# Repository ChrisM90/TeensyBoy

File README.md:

New best FPS achieved 5.7 :-) 

First revision PCB design complete and awaiting fabrication.

Do To's:

1) Finish sound implementation.
2) Serious optimization and code cleanup.
3) Gameboy colour compatibility.
4) Cartridge connector to play real games?
5) Functionality to rip ROM's to SD card?
6) Proper hardware explanation and documentation.

If you feel inclined to donate:
Bitcoin:  1EkhsVgQydefFFrJgEuCpkJ9TY6QsAo3og

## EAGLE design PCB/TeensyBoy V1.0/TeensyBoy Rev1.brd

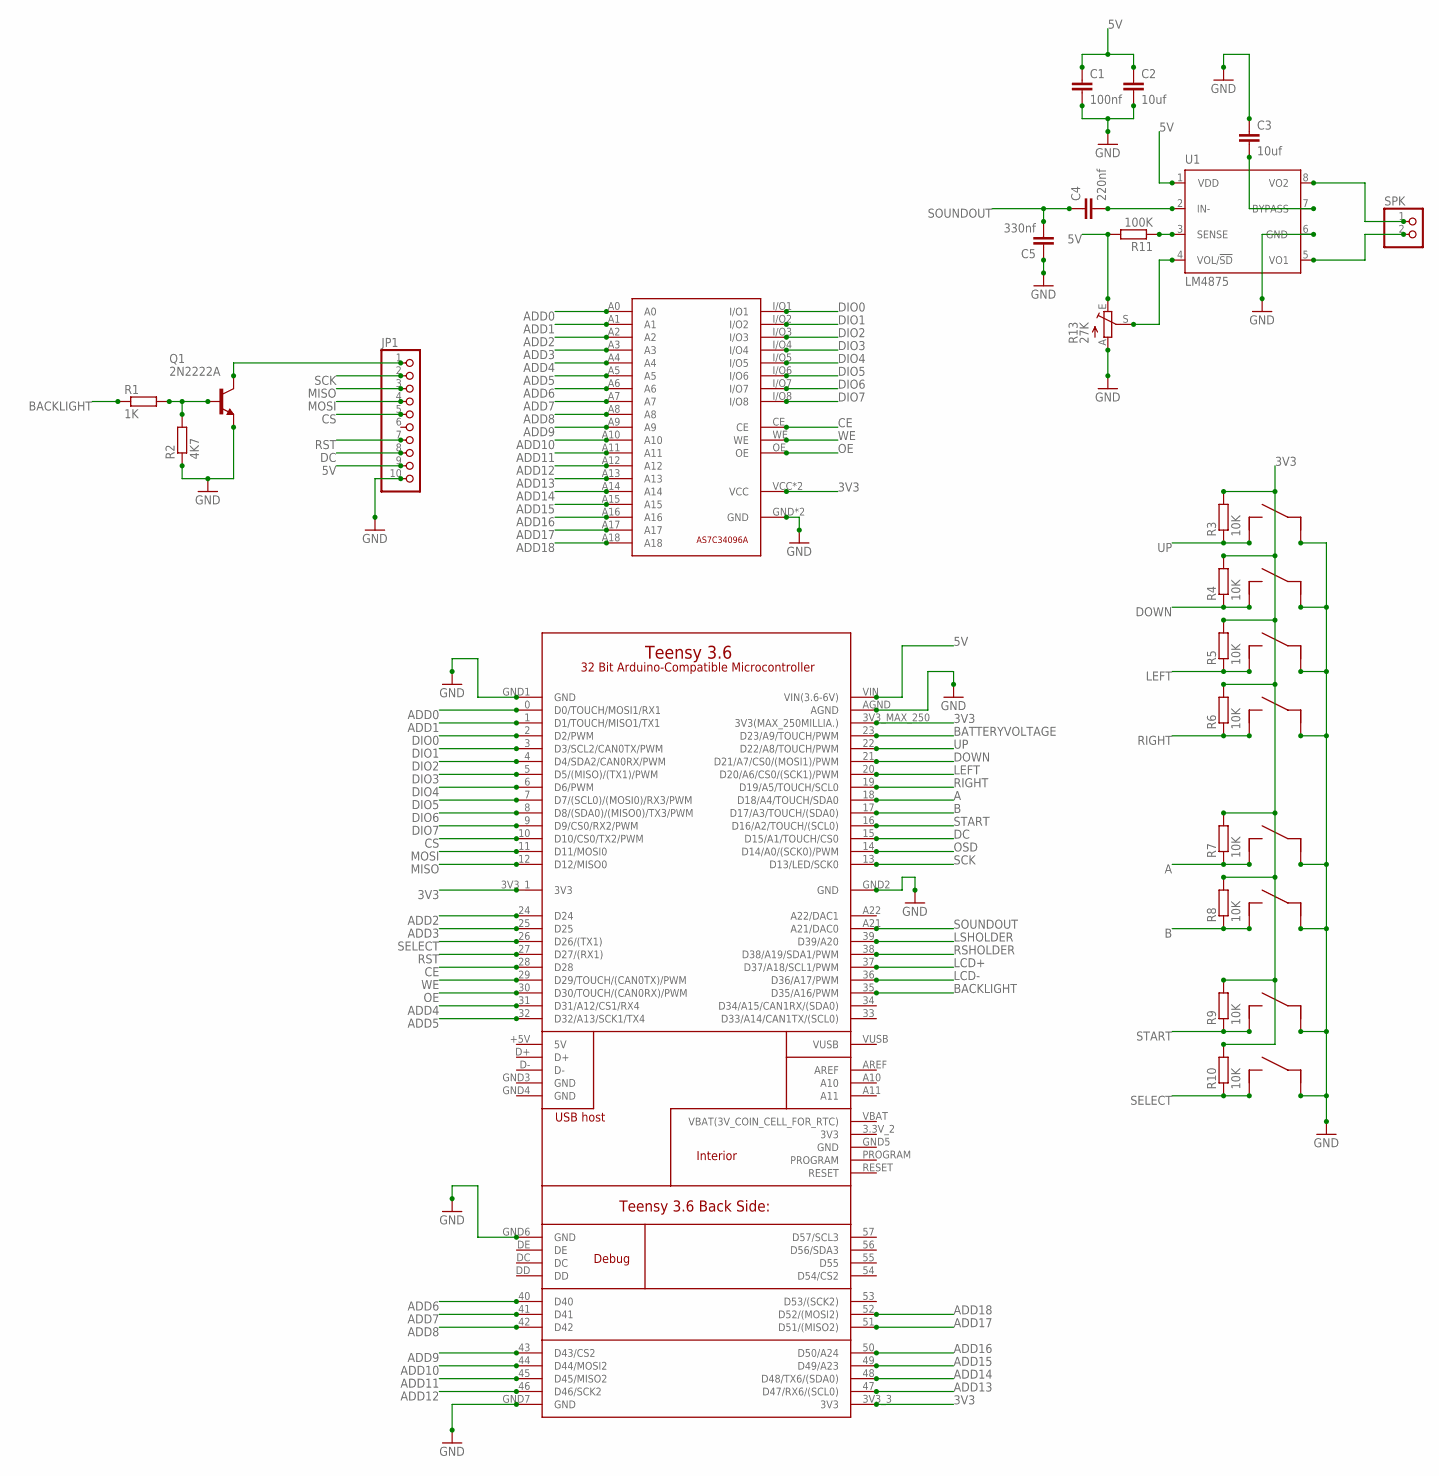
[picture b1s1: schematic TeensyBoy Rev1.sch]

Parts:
A: DTS-3
B: DTS-3
C1: 100nf; C0603K
C2, C3: 10uf; C0603K
C4: 220nf; C0603K
C5: 330nf; C0603K
DOWN: DTS-3
JP1: PINHD-1X10; 1X10
LEFT: DTS-3
Q1: 2N2222A; TO18
R1: 1K; R0603
R2: 4K7; R0603
R3, R4, R5, R6, R7, R8, R9, R10: 10K; R0603
R11: 100K; R0603
R13: 27K; CT6
RIGHT: DTS-3
SELECT: DTS-3
SPK: PINHD-1X2; 1X02
START: DTS-3
U1: LM4875; SO-8
U$1: AS7C34096A
U$2: TEENSY-3.6_FULL
UP: DTS-3

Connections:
3V3: R3.2, R4.2, R5.2, R6.2, R7.2, R8.2, R9.2, R10.2, U$1.VCC, U$1.VCC0 (VCC), U$2.3V3_1 (3V3), U$2.3V3_3 (3V3), U$2.3V3_MAX_250 (3V3(MAX_250MILLIA.))
5V: C1.1, C2.1, JP1.9, R11.2, R13.E, U1.1 (VDD), U$2.VIN (VIN(3.6-6V))
A: A.P$1, R7.1, U$2.18 (D18/A4/TOUCH/SDA0)
ADD0: U$1.A0, U$2.0 (D0/TOUCH/MOSI1/RX1)
ADD1: U$1.A1, U$2.1 (D1/TOUCH/MISO1/TX1)
ADD2: U$1.A2, U$2.24 (D24)
ADD3: U$1.A3, U$2.25 (D25)
ADD4: U$1.A4, U$2.31 (D31/A12/CS1/RX4)
ADD5: U$1.A5, U$2.32 (D32/A13/SCK1/TX4)
ADD6: U$1.A6, U$2.40 (D40)
ADD7: U$1.A7, U$2.41 (D41)
ADD8: U$1.A8, U$2.42 (D42)
ADD9: U$1.A9, U$2.43 (D43/CS2)
ADD10: U$1.A10, U$2.44 (D44/MOSI2)
ADD11: U$1.A11, U$2.45 (D45/MISO2)
ADD12: U$1.A12, U$2.46 (D46/SCK2)
ADD13: U$1.A13, U$2.47 (D47/RX6/(SCL0))
ADD14: U$1.A14, U$2.48 (D48/TX6/(SDA0))
ADD15: U$1.A15, U$2.49 (D49/A23)
ADD16: U$1.A16, U$2.50 (D50/A24)
ADD17: U$1.A17, U$2.51 (D51/(MISO2))
ADD18: U$1.A18, U$2.52 (D52/(MOSI2))
B: B.P$1, R8.1, U$2.17 (D17/A3/TOUCH/(SDA0))
BACKLIGHT: R1.1, U$2.35 (D35/A16/PWM)
BATTERYVOLTAGE: U$2.23 (D23/A9/TOUCH/PWM)
CE: U$1.CE, U$2.28 (D28)
CS: JP1.5, U$2.10 (D10/CS0/TX2/PWM)
DC: JP1.8, U$2.15 (D15/A1/TOUCH/CS0)
DIO0: U$1.I/O1, U$2.2 (D2/PWM)
DIO1: U$1.I/O2, U$2.3 (D3/SCL2/CAN0TX/PWM)
DIO2: U$1.I/O3, U$2.4 (D4/SDA2/CAN0RX/PWM)
DIO3: U$1.I/O4, U$2.5 (D5/(MISO)/(TX1)/PWM)
DIO4: U$1.I/O5, U$2.6 (D6/PWM)
DIO5: U$1.I/O6, U$2.7 (D7/(SCL0)/(MOSI0)/RX3/PWM)
DIO6: U$1.I/O7, U$2.8 (D8/(SDA0)/(MISO0)/TX3/PWM)
DIO7: U$1.I/O8, U$2.9 (D9/CS0/RX2/PWM)
DOWN: DOWN.P$1, R4.1, U$2.21 (D21/A7/CS0/(MOSI1)/PWM)
GND: A.P$2, B.P$2, C1.2, C2.2, C3.1, C5.1, DOWN.P$2, JP1.10, LEFT.P$2, Q1.1 (E), R2.1, R13.A, RIGHT.P$2, SELECT.P$2, START.P$2, U1.6 (GND), U$1.GND, U$1.GND0 (GND), U$2.AGND, U$2.GND1 (GND), U$2.GND2 (GND), U$2.GND6 (GND), U$2.GND7 (GND), UP.P$2
LCD+: U$2.37 (D37/A18/SCL1/PWM)
LCD-: U$2.36 (D36/A17/PWM)
LEFT: LEFT.P$1, R5.1, U$2.20 (D20/A6/CS0/(SCK1)/PWM)
LSHOLDER: U$2.39 (D39/A20)
MISO: JP1.3, U$2.12 (D12/MISO0)
MOSI: JP1.4, U$2.11 (D11/MOSI0)
unnamed: JP1.1, Q1.3 (C)
unnamed: Q1.2 (B), R1.2, R2.2
unnamed: C3.2, U1.7 (BYPASS)
unnamed: C4.2, U1.2 (IN-)
unnamed: R11.1, U1.3 (SENSE)
unnamed: SPK.1, U1.8 (VO2)
unnamed: SPK.2, U1.5 (VO1)
unnamed: R13.S, U1.4 (VOL/!SD)
OE: U$1.OE, U$2.30 (D30/TOUCH/(CAN0RX)/PWM)
OSD: U$2.14 (D14/A0/(SCK0)/PWM)
RIGHT: R6.1, RIGHT.P$1, U$2.19 (D19/A5/TOUCH/SCL0)
RSHOLDER: U$2.38 (D38/A19/SDA1/PWM)
RST: JP1.7, U$2.27 (D27/(RX1))
SCK: JP1.2, U$2.13 (D13/LED/SCK0)
SELECT: R10.1, SELECT.P$1, U$2.26 (D26/(TX1))
SOUNDOUT: C4.1, C5.2, U$2.A21 (A21/DAC0)
START: R9.1, START.P$1, U$2.16 (D16/A2/TOUCH/(SCL0))
UP: R3.1, U$2.22 (D22/A8/TOUCH/PWM), UP.P$1
WE: U$1.WE, U$2.29 (D29/TOUCH/(CAN0TX)/PWM)

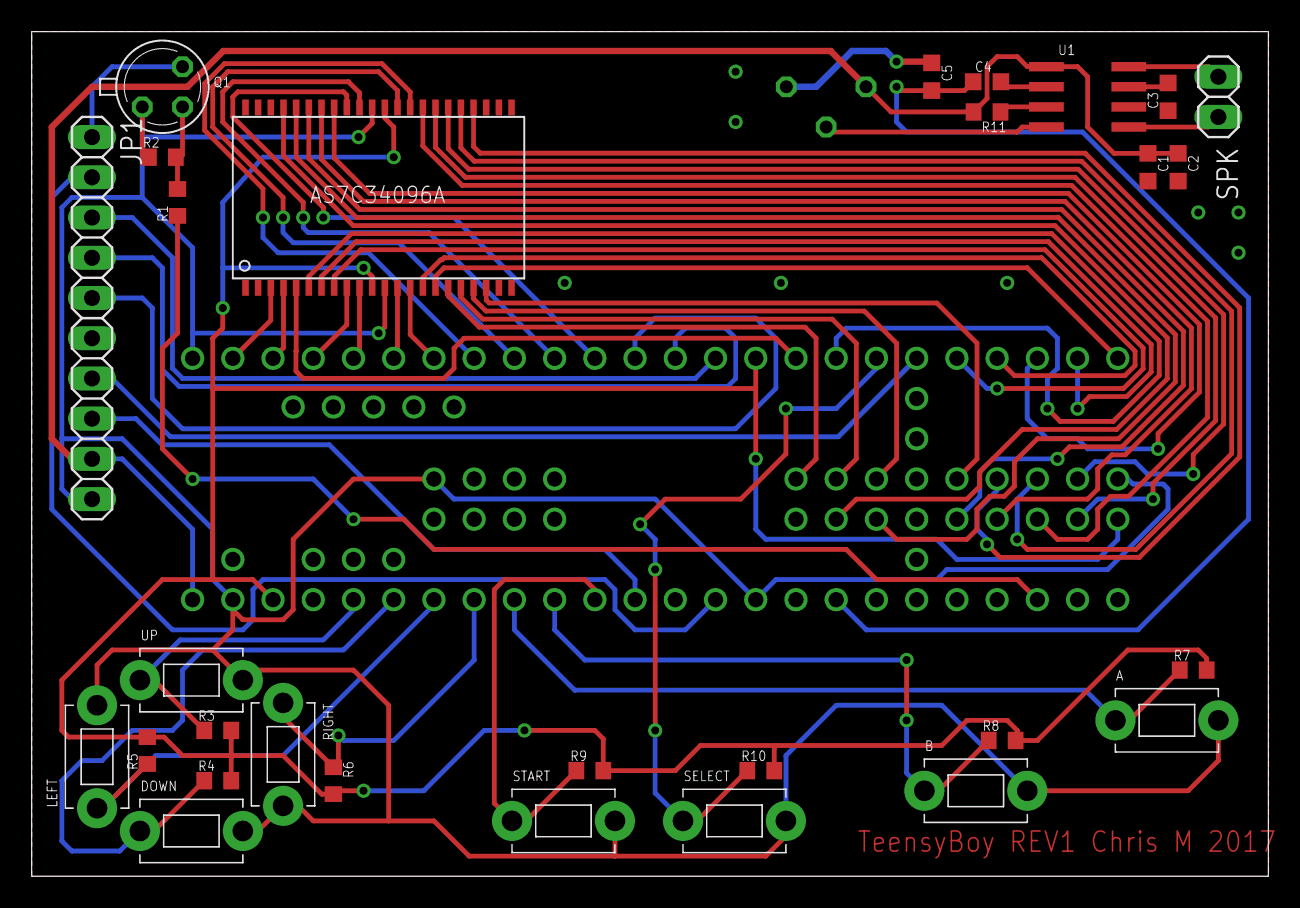
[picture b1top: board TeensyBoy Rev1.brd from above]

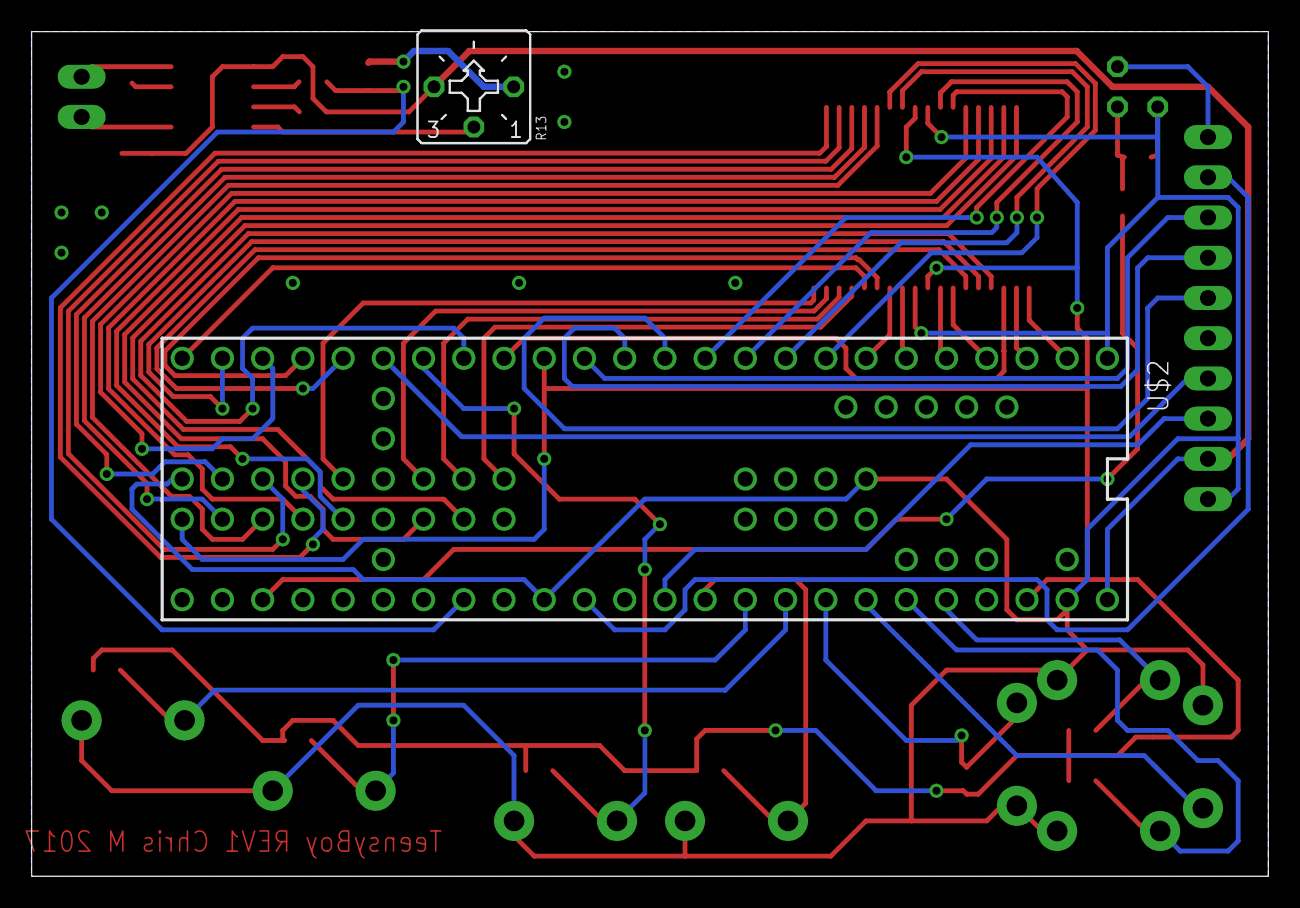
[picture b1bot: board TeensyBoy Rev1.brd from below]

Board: 2 copper layers, 78.1 x 53.3 mm, 31 parts (2 on the bottom side), 57 nets.

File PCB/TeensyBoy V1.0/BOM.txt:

Part     Value          Package

A        DTS-3          DTS-3
B        DTS-3          DTS-3
C1       100nf          C0603K
C2       10uf           C0603K
C3       10uf           C0603K
C4       220nf          C0603K
C5       330nf          C0603K
DOWN     DTS-3          DTS-3
JP1                     1X10
LEFT     DTS-3          DTS-3
Q1       2N2222A        TO18
R1       1K             R0603
R2       4K7            R0603
R3       10K            R0603
R4       10K            R0603
R5       10K            R0603
R6       10K            R0603
R7       10K            R0603
R8       10K            R0603
R9       10K            R0603
R10      10K            R0603
R11      100K           R0603
R13      27K            CT6
RIGHT    DTS-3          DTS-3
SELECT   DTS-3          DTS-3
SPK                     1X02
START    DTS-3          DTS-3 
U$1      AS7C34096A     AS7C34096A
U$2                     TEENSY-3.6_FULL
U1       LM4875         SO-8
UP       DTS-3          DTS-3

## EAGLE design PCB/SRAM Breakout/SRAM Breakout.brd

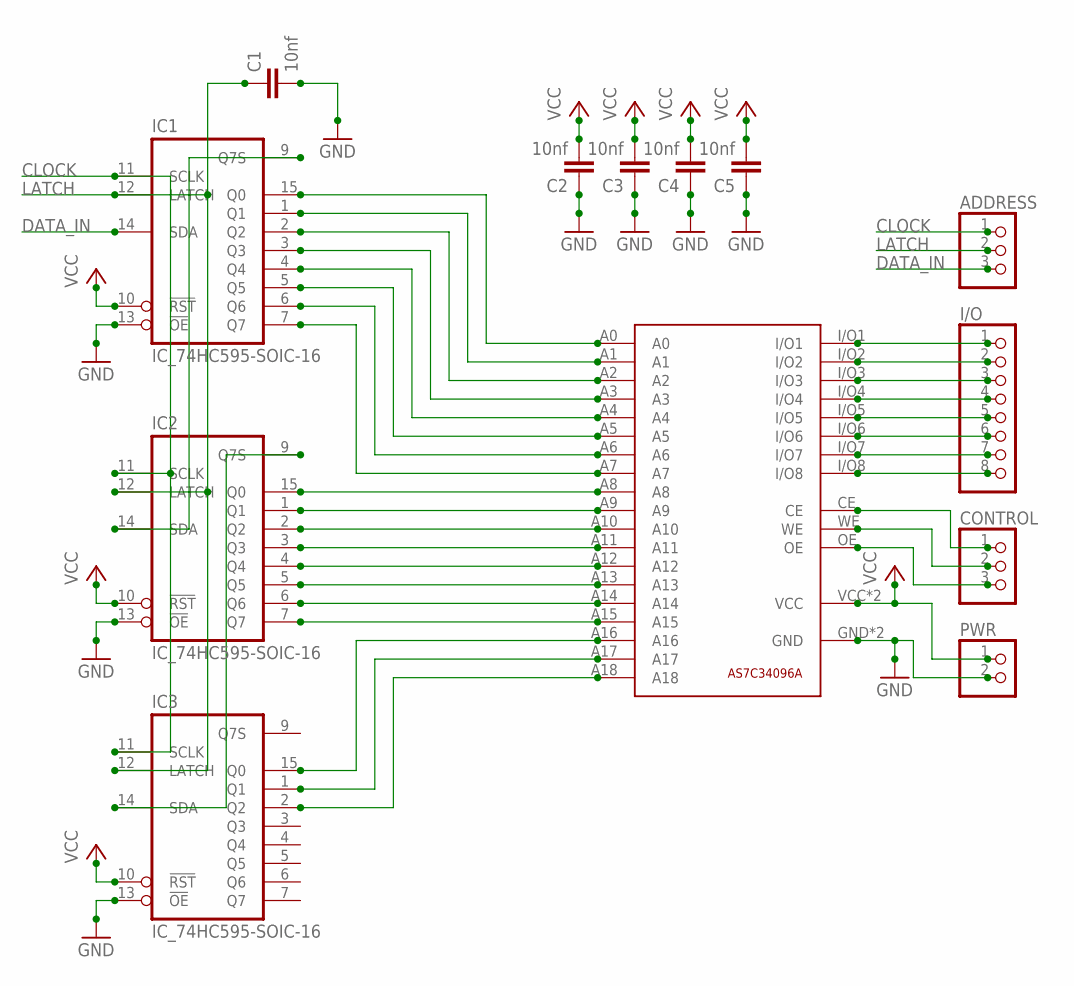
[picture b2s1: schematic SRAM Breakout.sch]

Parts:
ADDRESS: PINHD-1X3/90; 1X03/90
C1, C2, C3, C4, C5: 10nf; C0603
CONTROL: PINHD-1X3/90; 1X03/90
I/O: PINHD-1X8/90; 1X08/90
IC1, IC2, IC3: IC_74HC595-SOIC-16; SOIC-16
PWR: PINHD-1X2/90; 1X02/90
U$1: AS7C34096A

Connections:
CLOCK: ADDRESS.1, IC1.11 (SCLK), IC2.11 (SCLK), IC3.11 (SCLK)
DATA_IN: ADDRESS.3, IC1.14 (SDA)
GND: C1.2, C2.1, C3.1, C4.1, C5.1, IC1.13 (!OE), IC2.13 (!OE), IC3.13 (!OE), PWR.2, U$1.GND, U$1.GND0 (GND)
LATCH: ADDRESS.2, C1.1, IC1.12 (LATCH), IC2.12 (LATCH), IC3.12 (LATCH)
unnamed: IC1.9 (Q7S), IC2.14 (SDA)
unnamed: IC2.9 (Q7S), IC3.14 (SDA)
unnamed: I/O.1, U$1.I/O1
unnamed: IC1.15 (Q0), U$1.A0
unnamed: IC1.1 (Q1), U$1.A1
unnamed: IC1.2 (Q2), U$1.A2
unnamed: IC1.3 (Q3), U$1.A3
unnamed: IC1.4 (Q4), U$1.A4
unnamed: IC1.5 (Q5), U$1.A5
unnamed: IC1.6 (Q6), U$1.A6
unnamed: IC1.7 (Q7), U$1.A7
unnamed: IC2.15 (Q0), U$1.A8
unnamed: IC2.1 (Q1), U$1.A9
unnamed: IC2.2 (Q2), U$1.A10
unnamed: IC2.3 (Q3), U$1.A11
unnamed: IC2.4 (Q4), U$1.A12
unnamed: IC2.5 (Q5), U$1.A13
unnamed: IC2.6 (Q6), U$1.A14
unnamed: IC2.7 (Q7), U$1.A15
unnamed: IC3.15 (Q0), U$1.A16
unnamed: IC3.1 (Q1), U$1.A17
unnamed: IC3.2 (Q2), U$1.A18
unnamed: I/O.2, U$1.I/O2
unnamed: I/O.3, U$1.I/O3
unnamed: I/O.4, U$1.I/O4
unnamed: I/O.5, U$1.I/O5
unnamed: I/O.6, U$1.I/O6
unnamed: I/O.7, U$1.I/O7
unnamed: I/O.8, U$1.I/O8
unnamed: CONTROL.1, U$1.CE
unnamed: CONTROL.2, U$1.WE
unnamed: CONTROL.3, U$1.OE
VCC: C2.2, C3.2, C4.2, C5.2, IC1.10 (!RST), IC2.10 (!RST), IC3.10 (!RST), PWR.1, U$1.VCC, U$1.VCC0 (VCC)

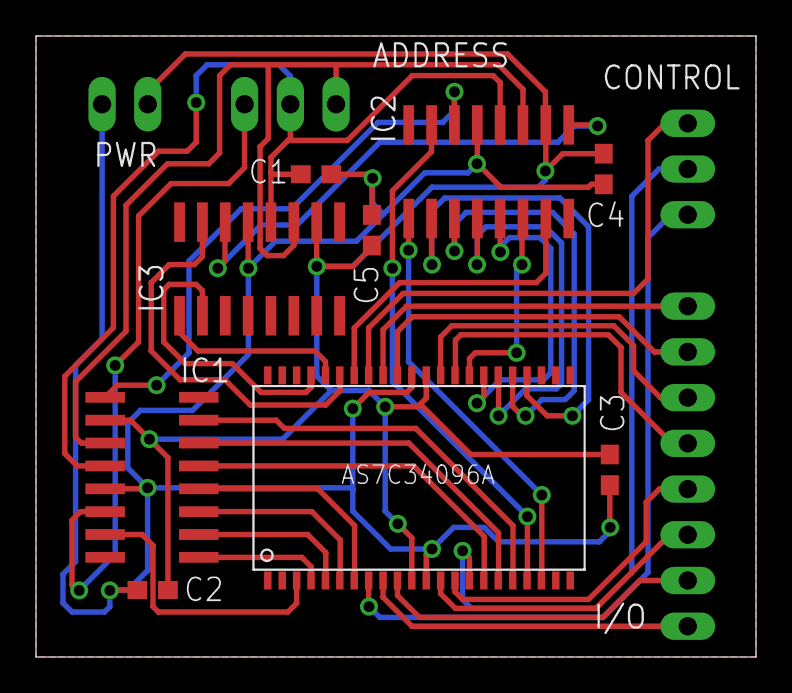
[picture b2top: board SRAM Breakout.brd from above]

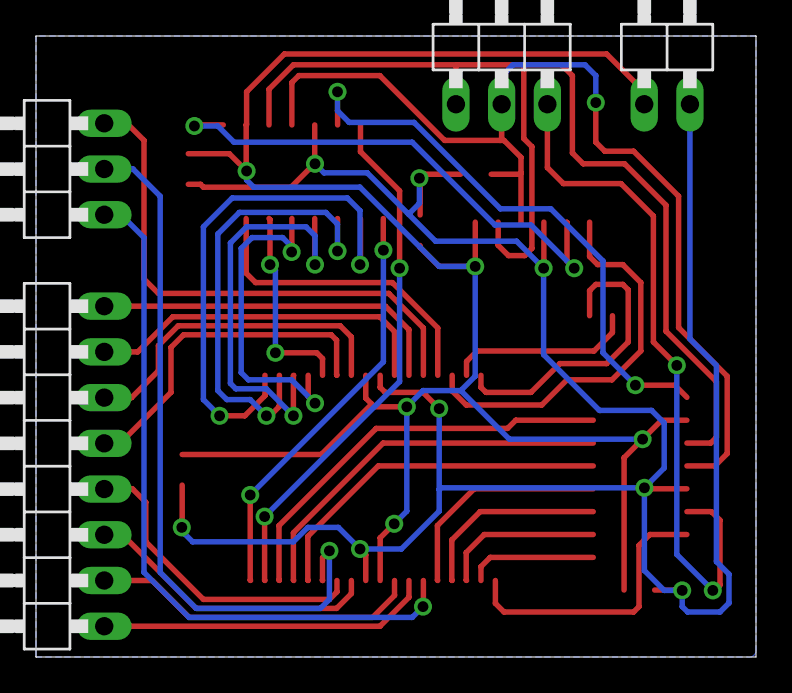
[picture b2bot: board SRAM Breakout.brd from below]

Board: 2 copper layers, 40.0 x 34.5 mm, 13 parts (4 on the bottom side), 37 nets.

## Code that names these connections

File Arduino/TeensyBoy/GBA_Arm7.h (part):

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  //Memory Address Time Seq: 0.40us
  
  //           BITMASK       PORTSET       PORTCLR
  // ADD0 0   //(1 << 16)    GPIOB_PSOR    GPIOB_PCOR
  // ADD1 1   //(1 << 17)    GPIOB_PSOR    GPIOB_PCOR
  // ADD2 24  //(1 << 26)    GPIOE_PSOR    GPIOE_PCOR
  // ADD3 25  //(1 << 5)     GPIOA_PSOR    GPIOA_PCOR
  // ADD4 31  //(1 << 10)    GPIOB_PSOR    GPIOB_PCOR
  // ADD5 32  //(1 << 11)    GPIOB_PSOR    GPIOB_PCOR
  // ADD6 40  //(1 << 28)    GPIOA_PSOR    GPIOA_PCOR
  // ADD7 41  //(1 << 29)    GPIOA_PSOR    GPIOA_PCOR 
  // ADD8 42  //(1 << 26)    GPIOA_PSOR    GPIOA_PCOR 
  // ADD9 43  //(1 << 20)    GPIOB_PSOR    GPIOB_PCOR
  // ADD10 44 //(1 << 22)    GPIOB_PSOR    GPIOB_PCOR
  // ADD11 45 //(1 << 23)    GPIOB_PSOR    GPIOB_PCOR
  // ADD12 46 //(1 << 21)    GPIOB_PSOR    GPIOB_PCOR
  // ADD13 47 //(1 << 8)     GPIOD_PSOR    GPIOD_PCOR 
  // ADD14 48 //(1 << 9)     GPIOD_PSOR    GPIOD_PCOR 
  // ADD15 49 //(1 << 4)     GPIOB_PSOR    GPIOB_PCOR
  // ADD16 50 //(1 << 5)     GPIOB_PSOR    GPIOB_PCOR 
  // ADD17 51 //(1 << 14)    GPIOD_PSOR    GPIOD_PCOR
  // ADD18 52 //(1 << 13)    GPIOD_PSOR    GPIOD_PCOR

  //GPIOB
  //Bit   24 23 22 21 20 19 18 17 16 15 14 13 12 11 10 9  8  7  6  5  4  3  2  1  0
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  }

  GPIOA_PCOR |= 12288; //Clear PORTA Data Lines
  GPIOA_PSOR |= (((value >> 1) & 0x03) << 12); //DIO1 & DIO2

  if(((value >> 3) & 0x01)) //DIO3
  {
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  }

  GPIOD_PCOR |= 12; //Clear PORTD Data Lines
  GPIOD_PSOR |= (((value >> 5) & 0x03) << 2); //DIO5 & DIO6

  if(((value >> 7) & 0x01)) //DIO7
  {
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  }

  //Read IO Pins
  value = (GPIOD_PDIR & (1 << 0) ? 1 : 0);            //DIO0
  value |= (((GPIOA_PDIR >> 12) & 0x03) << 1);        //DIO1 & DIO2
  value |= ((GPIOD_PDIR & (1 << 7) ? 1 : 0) << 3);    //DIO3
  value |= ((GPIOD_PDIR & (1 << 4) ? 1 : 0) << 4);    //DIO4
  value |= (((GPIOD_PDIR >> 2) & 0x03) << 5);         //DIO5 & DIO6
  value |= ((GPIOC_PDIR & (1 << 3) ? 1 : 0) << 7);    //DIO7
  
  return value;
}
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
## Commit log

2017-03-15 :space_invader: Added .gitattributes & .gitignore files
2017-03-15 SRAM Breakout Eagle Files Added
2017-03-16 Added Pinout Information
2017-03-16 IO Reg Moved to Teensy RAM Shiftout replaced
2017-03-17 Colour Blend Issues Fixed
2017-03-17 Skip Shift Registers Quick & Dirty
2017-03-17 Ports & Pin Numbers Identified, FPS Counter
2017-03-18 Added Eagle Libraries
2017-03-19 First Proper Dev Board Revision
2017-03-19 Comment Cleanup
2017-03-20 Changes to ROM Access
2017-03-21 BIOS ROM validation now works & ROM starts
2017-03-21 ROM fixes
2017-03-21 Some Fixes & Minor Cleanup
2017-03-21 GFX Bug Squashed
2017-03-21 GFX Bugs Squashed
2017-03-21 Debug Messages Removed
2017-03-21 More Debug Messages Removed
2017-03-22 Start of port manipulation changes
2017-03-22 More Port Stuff
2017-03-22 Port Manipulation Changes Complete
2017-03-22 Skip Bios Option Added
2017-03-23 Start Of Audio
2017-03-24 GFX Type Corrections and Buttons Added
2017-03-24 ROM Debugging in progress
2017-03-28 GFX Bug Squashed, ROM Now Plays Correctly :-)
2017-03-29 SRAM Access Speed Improvments
2017-04-01 GBA files organised ready for GBC code

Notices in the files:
Arduino/TeensyBoy/GBA_Arm7.h:
TeenyBoy code is placed under the MIT license
Copyright (c) 2017 Chris Mortimer
